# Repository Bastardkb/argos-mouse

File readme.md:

# Argos mouse

An ergonomic mouse with a trackpad.

Engineered to be a full mouse replacement solution with high-quality, custom-developed components.

# Disclaimer

**This is a work in progress and not meant for ordering yet.**

# Required components

## 3d prints

The STL files are included in this Github repository, in the `files` folder.

| Description      | File                    | Notes                      |
| ---------------- | ----------------------- | ----------------------- |
| Case | `main.3mf` | |
| Switch holder | `switches.3mf` | |
| Trackpad holder | `trackpad holder.3mf` |  |
| Tent | `tent.3mf` | Optional |
| Trackpad holder | `trackpad holder.3mf` |  |

## Hardware

You can get a kit from Bastard keyboards directly. Alternatively, you can source components yourself.

| Part name      | Amount                    | Notes                      |
| ---------------- | ----------------------- | ----------------------- |
| Heated screw insert, M3x5x5 | 2 |  |
| M3 8mm torx screw | 3 | |
| M3 square nut | 1 | |
| Cirque trackpad | 1 | 40mm curved || 12-position FPC cable, 0.5mm pitch, same side contacts | 1      | Farnell, length TBD       |

Optional parts if you're using the tents

| Part name      | Amount                    | Notes                      |
| ---------------- | ----------------------- | ----------------------- |
| Heated screw insert, M3x5x5 | 3 |  |
| M3 8mm torx screw | 3 | |

## PCBs

You will need 2 PCBs for this mouse.

### Controller

- A RP2040-based board, the brain of the mouse
- The release section includes gerbers, BOM and POS files
- Order in 1.2mm thickness

### Switches

- Connects all the switches and add per-key RGB capabilities
- https://github.com/Bastardkb/argos-switches-pcb
- Order in 0.6mm thickness
- You can also instead handsolder or use amoebas, but then might have to modify the firmware.

## Print instructions

- Material: PLA
- Layer height: .15mm or .2mm
- Supports: everywhere*

*If using prusaslicer, using auto-painted supports will work as well.

# Build guide

You can find detailed instruction on the online documentation linked below.

# Links

- Discord: https://bastardkb.com/discord
- Website: https://bastardkb.com/
- Docs: https://docs.bastardkb.com

# License 

This work is licensed under a Creative Commons Attribution-NonCommercial-ShareAlike 4.0 International License.

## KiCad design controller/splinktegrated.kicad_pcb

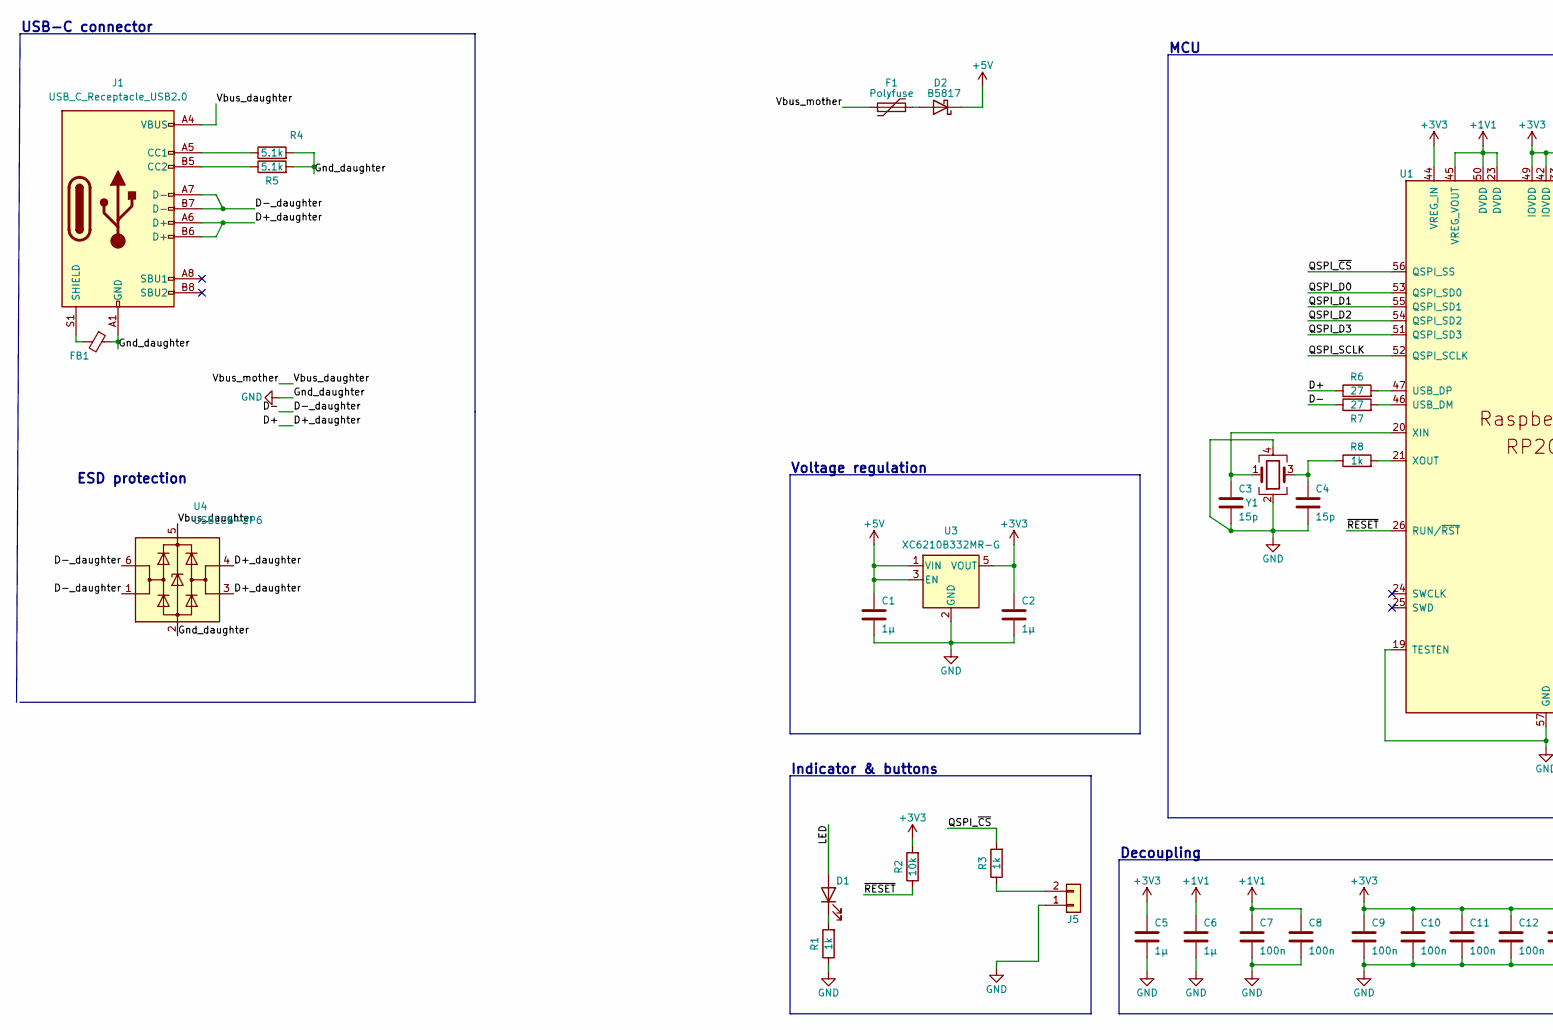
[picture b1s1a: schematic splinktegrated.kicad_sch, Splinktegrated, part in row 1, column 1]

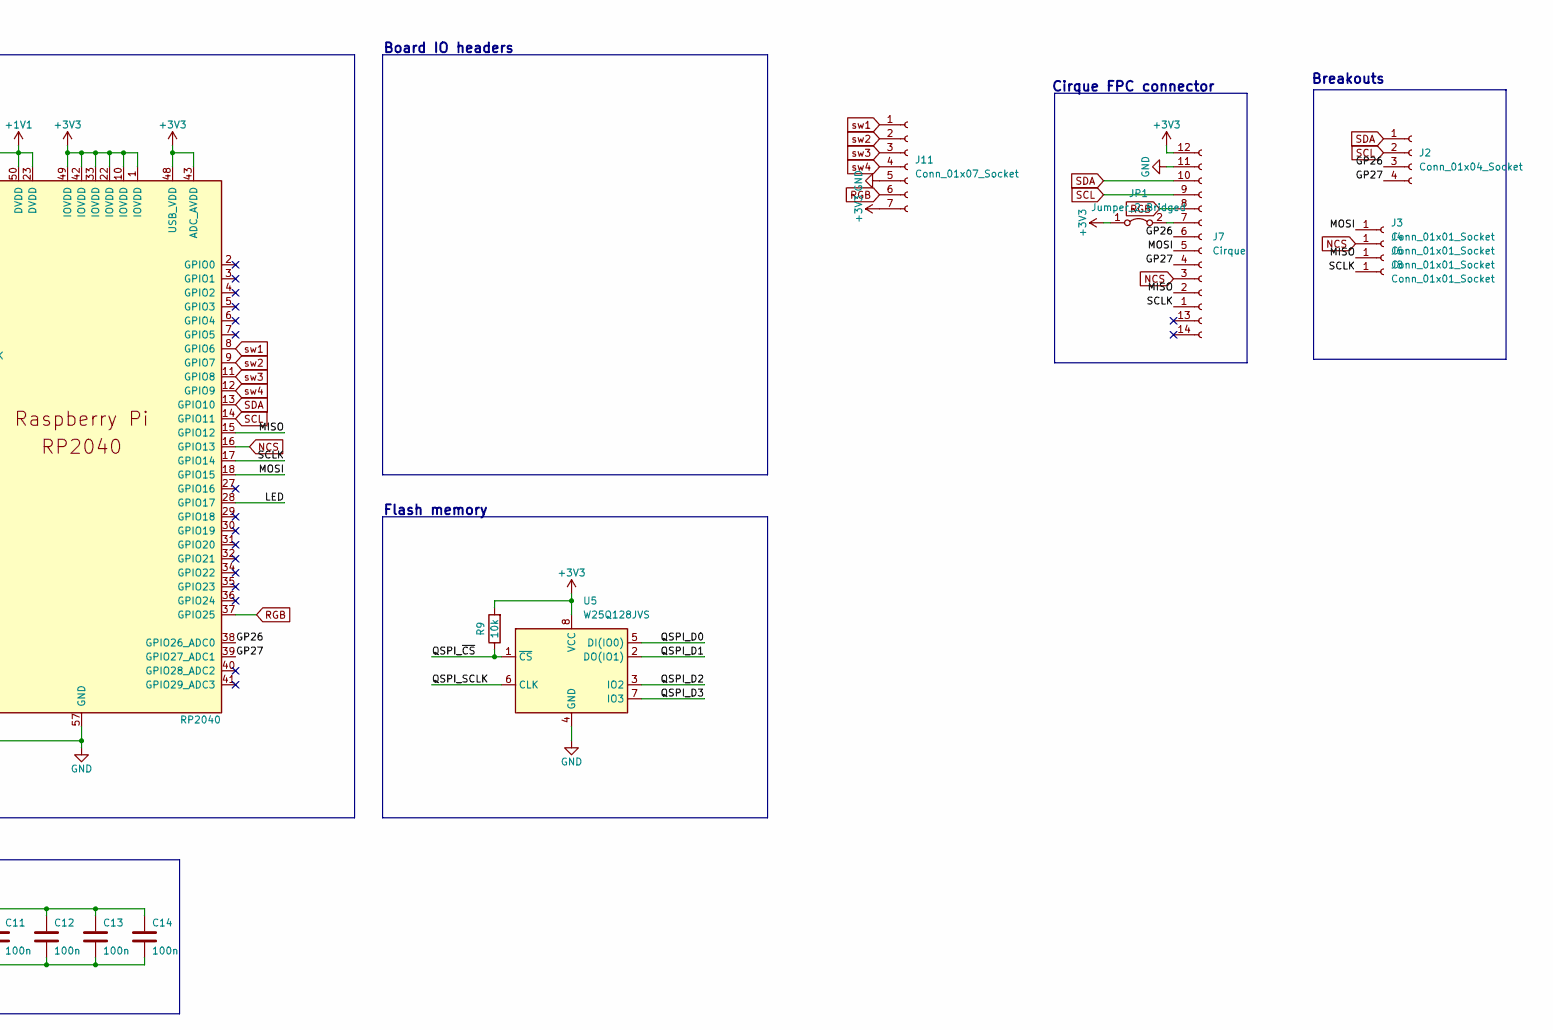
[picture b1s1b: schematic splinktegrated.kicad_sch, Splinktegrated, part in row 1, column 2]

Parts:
C1, C2: 1µ; C_0603_1608Metric; LCSC C19666
C3, C4: 15p; C_0402_1005Metric; LCSC C1548
C5, C6: 1µ; C_0402_1005Metric; LCSC C52923
C7, C8, C9, C10, C11, C12, C13, C14: 100n; C_0402_1005Metric; LCSC C1525
D1: LED; LED_0402_1005Metric; LCSC C130719
D2: B5817; D_SOD-323; LCSC C123899
F1: Polyfuse; Fuse_0603_1608Metric; LCSC C69679
FB1: FerriteBead_Small; L_0603_1608Metric; LCSC C98288
J1: USB_C_Receptacle_USB2.0; GT-USB-7014C; LCSC C223907
J2: Conn_01x04_Socket; PinSocket_1x04_P2.54mm_Vertical
J3, J4, J6, J8: Conn_01x01_Socket; PinHeader_1x01_P1.27mm_SMD
J5: Conn_01x02; PinHeader_1x02_P1.27mm_Vertical
J7: Cirque; FPC-SMD_FPC05012-09200-.5mm
J11: Conn_01x07_Socket; PinSocket_1x07_P2.54mm_Vertical
JP1: Jumper_2_Bridged; SolderJumper-2_P1.3mm_Open_RoundedPad1.0x1.5mm
R1, R3, R8: 1k; R_0402_1005Metric; LCSC C11702
R2, R9: 10k; R_0402_1005Metric; LCSC C25744
R4, R5: 5.1k; R_0402_1005Metric; LCSC C25905
R6, R7: 27; R_0402_1005Metric; LCSC C25100
U1: RP2040; QFN-56-1EP_7x7mm_P0.4mm_EP3.2x3.2mm; LCSC C2040
U3: XC6210B332MR-G; SOT-23-5; LCSC C82942
U4: USBLC6-2P6; SOT-666
U5: W25Q128JVS; W25Q128JVPIQ
Y1: Crystal_GND24; Crystal_SMD_2520-4Pin_2.5x2.0mm; LCSC C2149204

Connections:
+1V1: C6.1, C7.1, C8.1, U1.23 (DVDD), U1.45 (VREG_VOUT), U1.50 (DVDD)
+3V3: C2.1, C5.1, C9.1, C10.1, C11.1, C12.1, C13.1, C14.1, J7.12, J11.7, JP1.1 (A), R2.2, R9.2, U1.1 (IOVDD), U1.10 (IOVDD), U1.22 (IOVDD), U1.33 (IOVDD), U1.42 (IOVDD), U1.43 (ADC_AVDD), U1.44 (VREG_IN), U1.48 (USB_VDD), U1.49 (IOVDD), U3.5 (VOUT), U5.8 (VCC)
+5V: C1.1, D2.1 (K), U3.1 (VIN), U3.3 (EN)
/D+: J1.A6 (D+), J1.B6 (D+), R6.1, U4.3 (I/O2), U4.4 (I/O2)
/D-: J1.A7 (D-), J1.B7 (D-), R7.1, U4.1 (I/O1), U4.6 (I/O1)
/GP26: J2.3, J7.6, U1.38 (GPIO26_ADC0)
/GP27: J2.4, J7.4, U1.39 (GPIO27_ADC1)
/LED: D1.2 (A), U1.28 (GPIO17)
/MISO: J6.1, J7.2, U1.15 (GPIO12)
/MOSI: J3.1, J7.5, U1.18 (GPIO15)
/QSPI_D0: U1.53 (QSPI_SD0), U5.5 (DI(IO0))
/QSPI_D1: U1.55 (QSPI_SD1), U5.2 (DO(IO1))
/QSPI_D2: U1.54 (QSPI_SD2), U5.3 (IO2)
/QSPI_D3: U1.51 (QSPI_SD3), U5.7 (IO3)
/QSPI_SCLK: U1.52 (QSPI_SCLK), U5.6 (CLK)
/QSPI_~CS: R3.2, R9.1, U1.56 (QSPI_SS), U5.1 (~CS)
/SCLK: J7.1, J8.1, U1.17 (GPIO14)
/Vbus_daughter: F1.1, J1.A4 (VBUS), J1.A9 (VBUS), J1.B4 (VBUS), J1.B9 (VBUS), U4.5 (VBUS)
/~RESET: R2.1, U1.26 (RUN/~RST)
GND: C1.2, C2.2, C3.2, C4.2, C5.2, C6.2, C7.2, C8.2, C9.2, C10.2, C11.2, C12.2, C13.2, C14.2, FB1.1, J1.A1 (GND), J1.A12 (GND), J1.B1 (GND), J1.B12 (GND), J5.1, J7.11, J11.5, R1.1, R4.2, R5.2, U1.19 (TESTEN), U1.57 (GND), U3.2 (GND), U4.2 (GND), U5.4 (GND), Y1.2, Y1.4
NCS: J4.1, J7.3, U1.16 (GPIO13)
unnamed: C4.1, R8.1, Y1.3
unnamed: D1.1 (K), R1.2
unnamed: D2.2 (A), F1.2
unnamed: J1.A5 (CC1), R4.1
unnamed: J1.B5 (CC2), R5.1
unnamed: FB1.2, J1.S1 (SHIELD)
unnamed: J5.2, R3.1
unnamed: J7.7, JP1.2 (B)
unnamed: R7.2, U1.46 (USB_DM)
unnamed: R6.2, U1.47 (USB_DP)
unnamed: C3.1, U1.20 (XIN), Y1.1
unnamed: R8.2, U1.21 (XOUT)
RGB: J7.8, J11.6, U1.37 (GPIO25)
SCL: J2.2, J7.9, U1.14 (GPIO11)
SDA: J2.1, J7.10, U1.13 (GPIO10)
sw1: J11.1, U1.8 (GPIO6)
sw2: J11.2, U1.9 (GPIO7)
sw3: J11.3, U1.11 (GPIO8)
sw4: J11.4, U1.12 (GPIO9)

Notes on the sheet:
Decoupling
Board IO headers
USB-C connector
Cirque FPC connector
Indicator & buttons
ESD protection
Voltage regulation
Breakouts
MCU
Flash memory

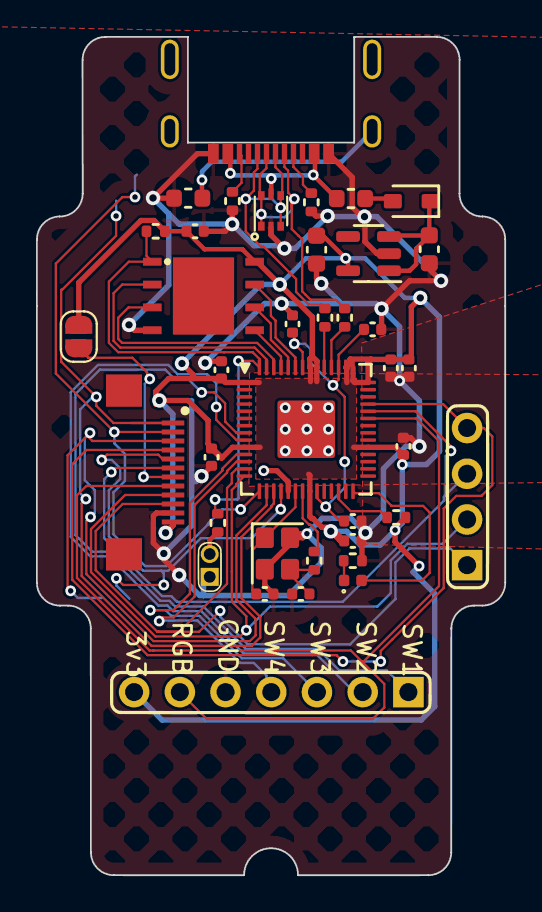
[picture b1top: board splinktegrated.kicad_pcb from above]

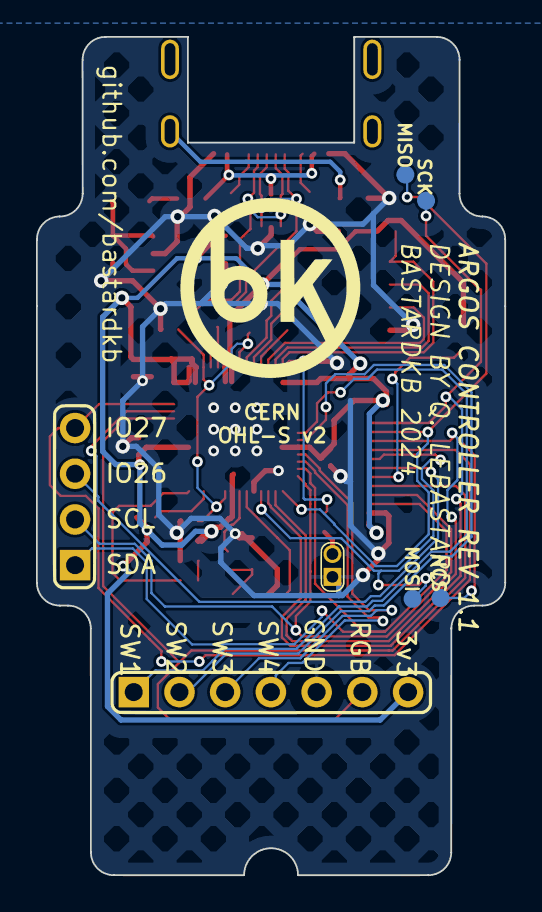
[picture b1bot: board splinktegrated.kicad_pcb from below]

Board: 2 copper layers, 26.0 x 46.6 mm, 42 parts (4 on the bottom side), 40 nets.

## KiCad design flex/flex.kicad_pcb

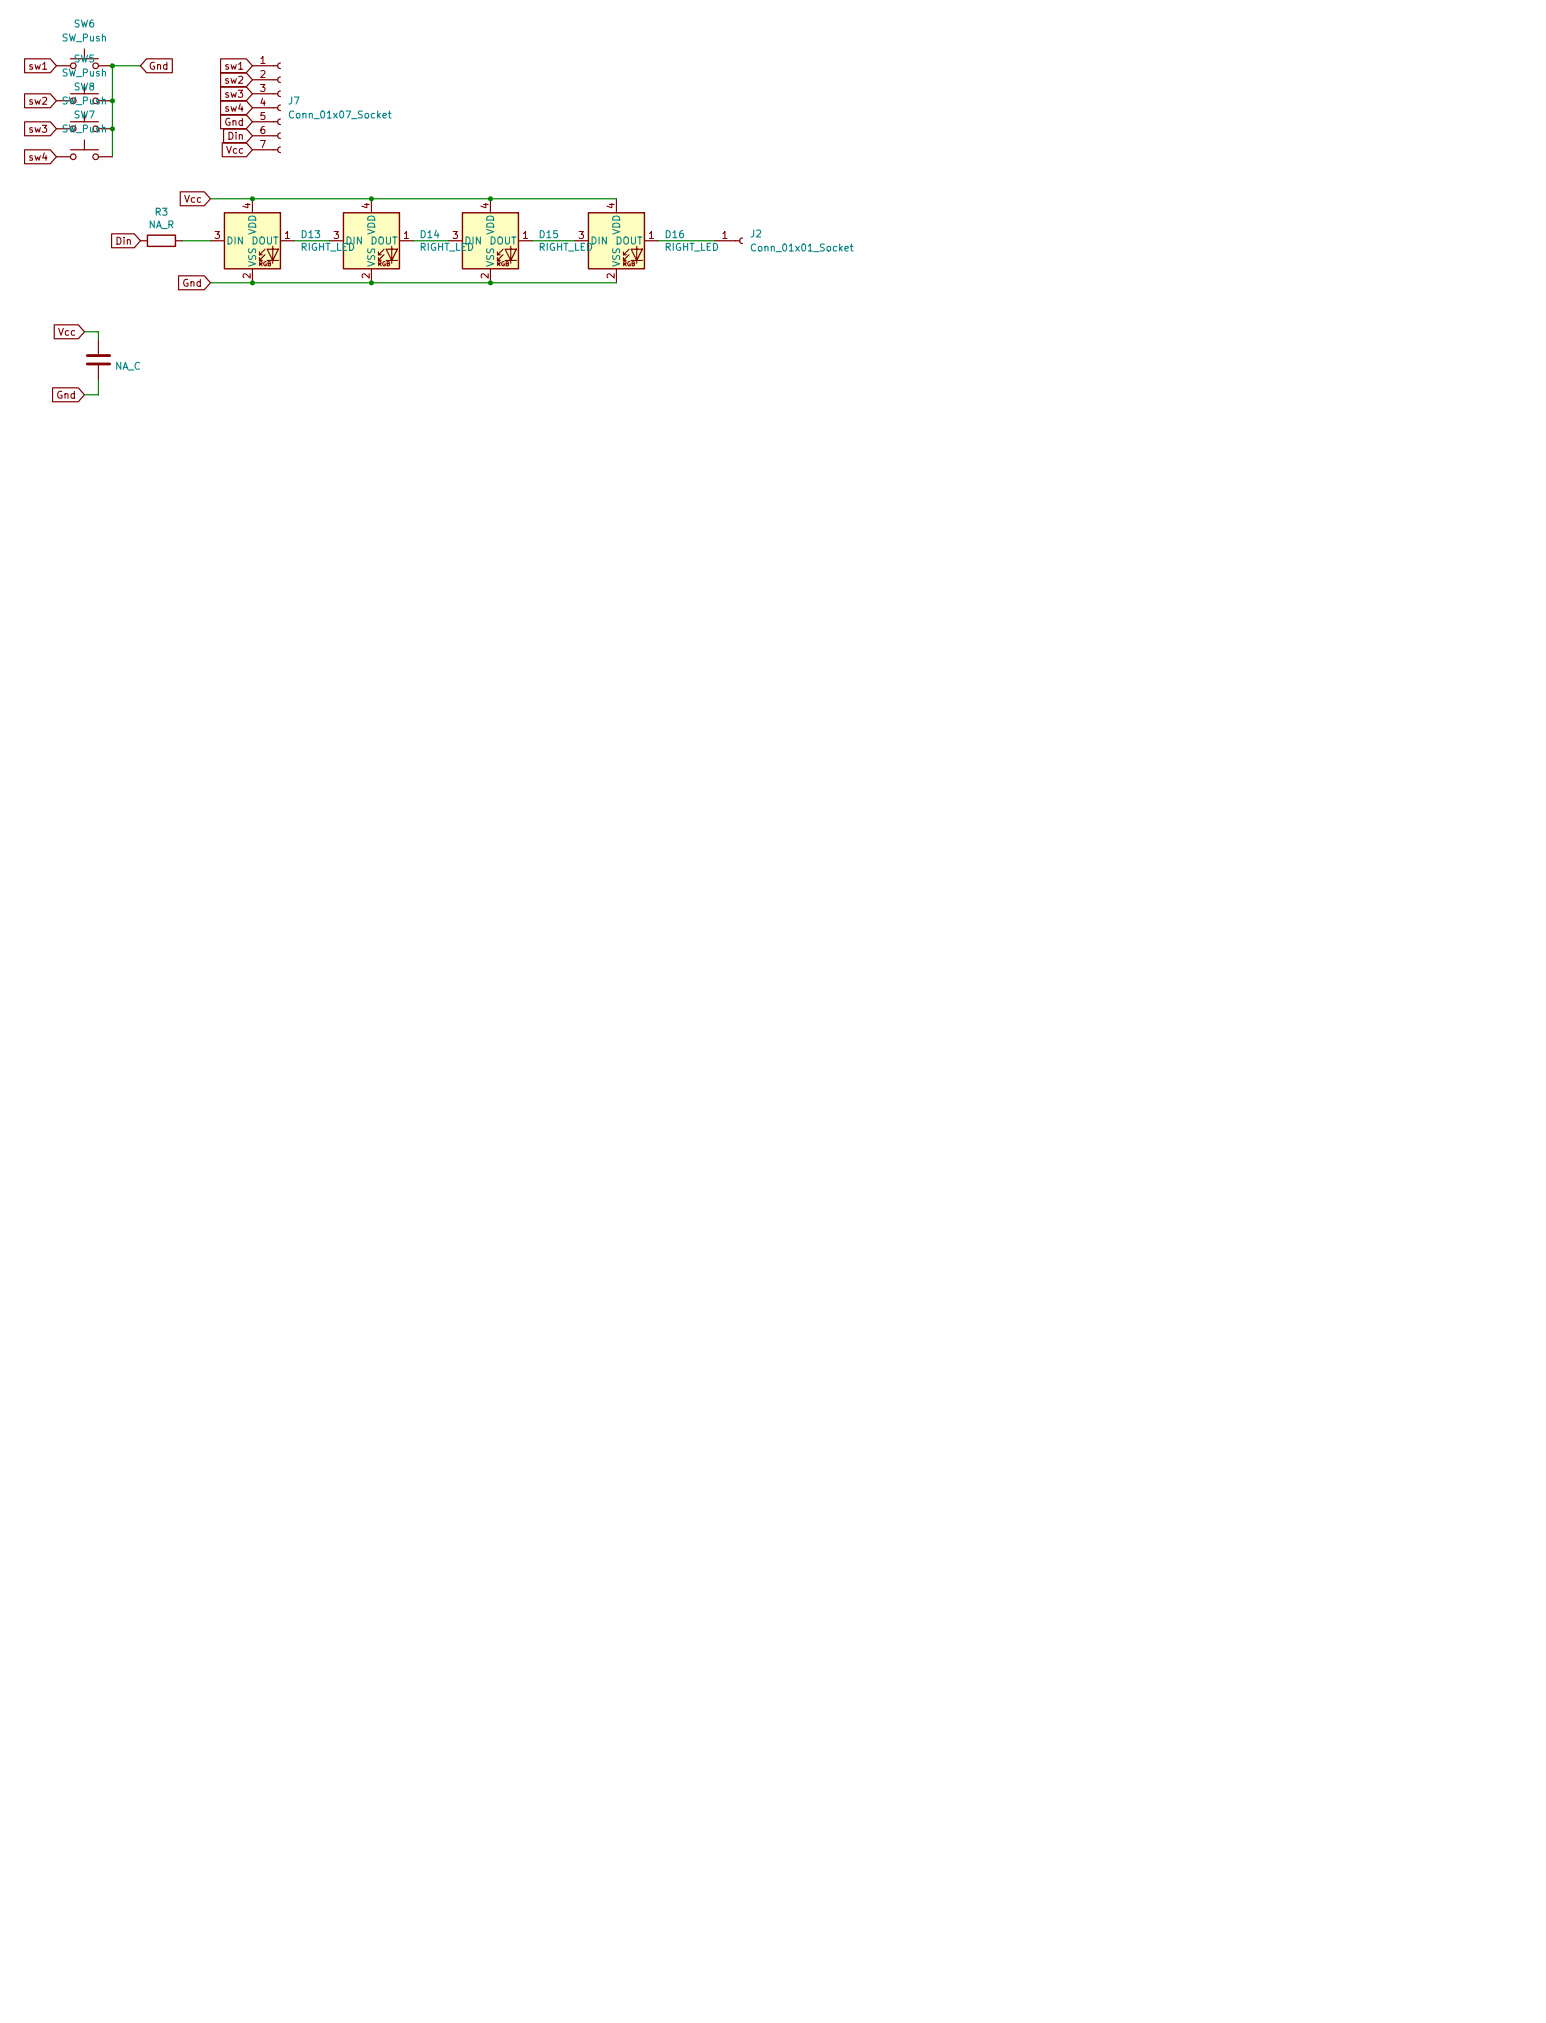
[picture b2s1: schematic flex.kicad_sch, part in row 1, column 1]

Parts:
C3: NA_C; C_SOD123
D13, D14, D15, D16: RIGHT_LED; SK6812_mini_e_corners
J2: Conn_01x01_Socket; PinHeader_1x01_P2.54mm_Vertical
J7: Conn_01x07_Socket; PinHeader_1x07_P2.54mm_Vertical
R3: NA_R; R_SOD123
SW5, SW6, SW7, SW8: SW_Push; choc

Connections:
Din: J7.6, R3.1
Gnd: C3.2, D13.2 (VSS), D14.2 (VSS), D15.2 (VSS), D16.2 (VSS), J7.5, SW5.2, SW6.2, SW7.2, SW8.2
unnamed: D13.3 (DIN), R3.2
unnamed: D13.1 (DOUT), D14.3 (DIN)
unnamed: D14.1 (DOUT), D15.3 (DIN)
unnamed: D15.1 (DOUT), D16.3 (DIN)
unnamed: D16.1 (DOUT), J2.1
Vcc: C3.1, D13.4 (VDD), D14.4 (VDD), D15.4 (VDD), D16.4 (VDD), J7.7
sw1: J7.1, SW6.1
sw2: J7.2, SW5.1
sw3: J7.3, SW8.1
sw4: J7.4, SW7.1

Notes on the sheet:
This work is licensed under a Creative Commons Attribution-NonCommercial-ShareAlike 4.0 International License.

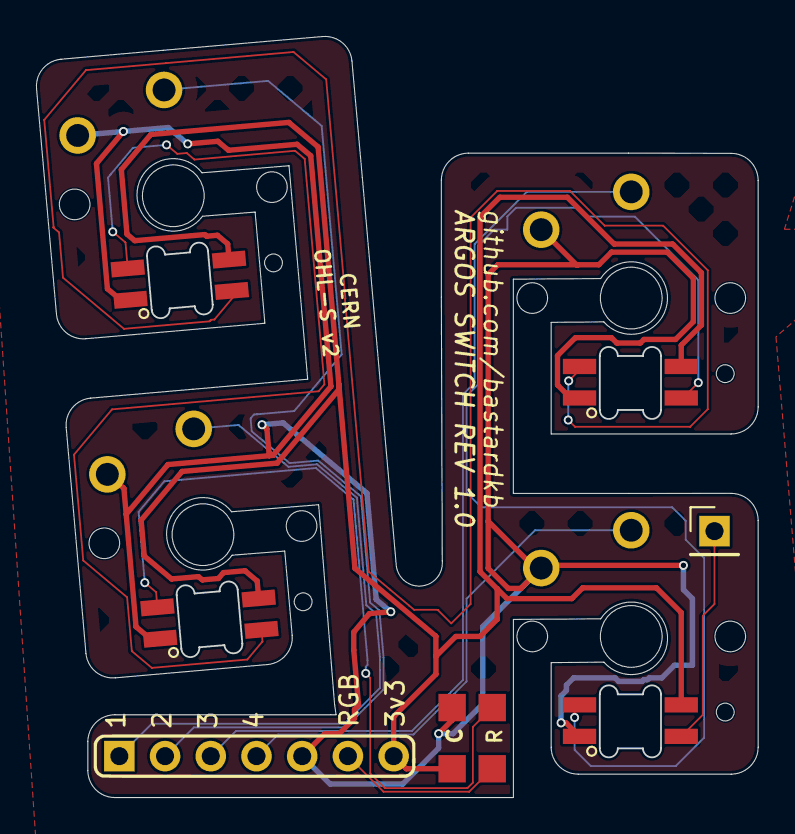
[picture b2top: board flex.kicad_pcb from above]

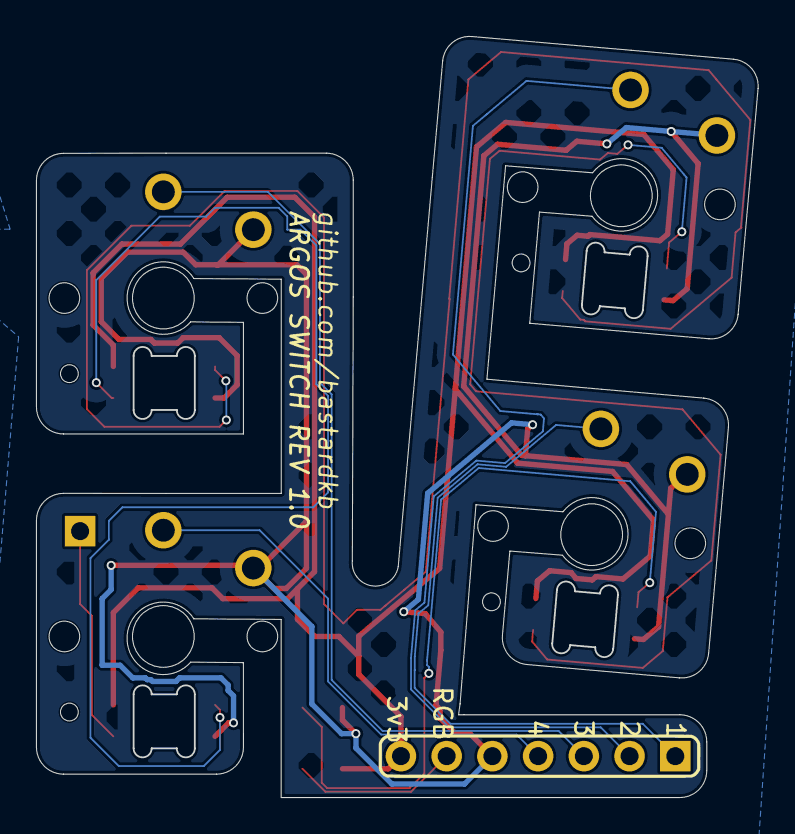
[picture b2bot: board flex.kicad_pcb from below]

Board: 2 copper layers, 40.1 x 42.3 mm, 12 parts (4 on the bottom side), 12 nets.

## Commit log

2024-05-24 files
2024-05-24 add controller
2024-05-24 routing
2024-05-24 work
2024-05-25 remove vbus detect
2024-05-25 flex PCB
2024-05-27 angle PCB
2024-05-27 details
2024-05-27 3d work
2024-06-14 5mm longer controller
2024-06-18 revert connector
2024-06-18 change SCK pin
2024-06-18 update USB BOM
2024-06-18 add trackpad breakouts
2024-06-18 version number
2024-06-20 remove flex
2024-06-25 update 3d models

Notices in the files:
flex/flex.kicad_sch:
CC BY-NC-SA 4.0
Copyright Quentin Lebastard 2022
